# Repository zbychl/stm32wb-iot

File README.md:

# STM32WB based IoT Project
This repisitory keeps components for IoT project based on STM32WB SoC. Project could be used as IoT sensor, effector, bridge, etc. 

# Project Components
Below there is a list of project components along with their description (PCB design for IoT board - HW, firmware - FW, software - SW, and documentation - DOC) . 

## HW - IoT board based on STM32WB SoC
Board designed for IoT sensor or effector. It is based on STM32WB SoC. Board design supports components listed below. Some of them are optional. 

### HW Components:
* STM32WB55CGU6 - dual ARM SoC with radio (BLE and IEEE 802.15.4)
* SHTC3 - digital (I2C) temperature and humidity sensor
* Switch(es)
* PCB antenna
* CR2032/LIR2032 or CR3032/LIR3032 battery socket
* Pins for external power supplier
* Test Points (TPs) for UART for update
* TPs for UART for console
* TPs for JTAG
* TP for HW reset
* LED(s) for health/status monitoring
* GPIO exposed on pins to support common interface (I2C, SPI, UART)
* TPS630xx for supplying from battery, alternatively, components supporting low voltages could be used
* EEPROM

### PCB details
There is a list of requirements put for PCB:
* Size: tbd
* Stackup:
  * https://jlcpcb.com/impedance
  * Layers: 4
  * Width: 1.6mm
  * Prepeg: 7628 (Fr=4.6)
* Standard SMT elements size: 0402 

## FW
TBD

## SW
TBD

## DOC
TBD

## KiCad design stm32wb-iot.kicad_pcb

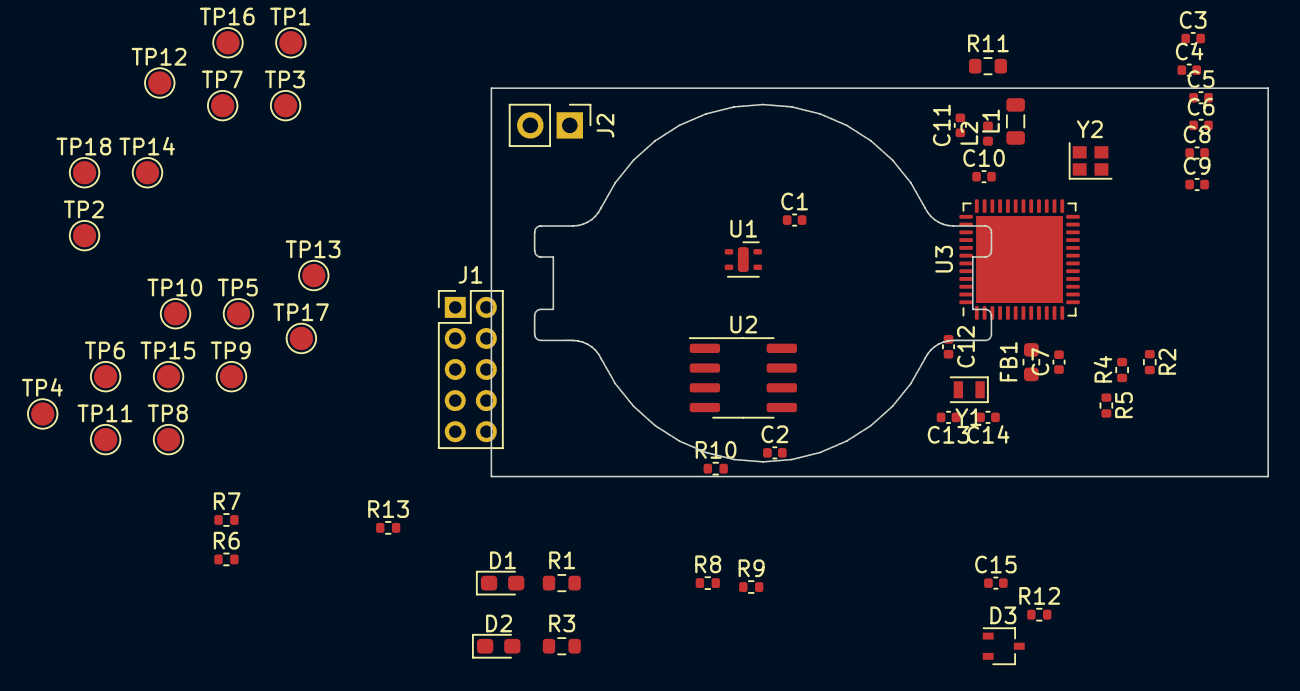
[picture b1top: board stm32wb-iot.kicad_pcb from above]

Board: 4 copper layers, 50.0 x 25.0 mm, 60 parts (1 on the bottom side), 34 nets, no tracks yet.

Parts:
BT1: Battery_Cell; BatteryHolder_Keystone_1057_1x2032
C1, C2, C3, C4, C5, C6, C7, C8, C9, C15: 100n/X5R; C_0402_1005Metric
C10, C11: 4.7uF/X5R; C_0402_1005Metric
C12: 100n\X7R; C_0402_1005Metric
C13, C14: 12pF; C_0402_1005Metric
D1, D2: LED; LED_0603_1608Metric_Pad1.05x0.95mm_HandSolder
D3: BAT54W; SOT-323_SC-70
FB1: 500mA/500mΩ; L_0603_1608Metric
J1: Conn_02x05_Odd_Even; PinHeader_2x05_P2.00mm_Vertical
J2: Conn_01x02_Male; PinHeader_1x02_P2.54mm_Vertical
L1: 10uH/100mA/20%; L_0805_2012Metric
L2: 10uH/500mA/5%; L_0402_1005Metric
R1, R3: 2k; R_0603_1608Metric
R2, R4, R5: 33R; R_0402_1005Metric
R6, R7, R8, R9, R10, R12, R13: 10k; R_0402_1005Metric
R11: 0R/250mW; R_0603_1608Metric
TP1: MISC_RX; TestPoint_Pad_D1.5mm
TP2: MISC_TX; TestPoint_Pad_D1.5mm
TP3, TP6, TP8, TP13, TP18: GND; TestPoint_Pad_D1.5mm
TP4: MISC_SCL; TestPoint_Pad_D1.5mm
TP5: MISC_SDA; TestPoint_Pad_D1.5mm
TP7: MISC_NRST; TestPoint_Pad_D1.5mm
TP9: MISC_BOOT0; TestPoint_Pad_D1.5mm
TP10, TP17: VDD; TestPoint_Pad_D1.5mm
TP11: MISC_IO0; TestPoint_Pad_D1.5mm
TP12: MISC_IO1; TestPoint_Pad_D1.5mm
TP14: SWDIO; TestPoint_Pad_D1.5mm
TP15: SWCLK; TestPoint_Pad_D1.5mm
TP16: NRST; TestPoint_Pad_D1.5mm
U1: SHTC3; Sensirion_DFN-4-1EP_2x2mm_P1mm_EP0.7x1.6mm
U2: M24C02-RMN; SOIC-8_3.9x4.9mm_P1.27mm
U3: STM32WB55Cx; QFN-48-1EP_7x7mm_P0.5mm_EP5.6x5.6mm
Y1: 32.768kHz; Crystal_SMD_2012-2Pin_2.0x1.2mm
Y2: 32MHz; Crystal_SMD_2016-4Pin_2.0x1.6mm

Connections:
/BOOT0: R13.1, TP9.1, U3.4 (PH3-BOOT0)
/IO_IO0: R4.1, U3.10 (PA1)
/IO_IO1: R2.1, U3.15 (PA6)
/IO_LED0: D1.1 (K), U3.17 (PA8)
/IO_LED1: D2.1 (K), U3.37 (PA11)
/IO_PWM: R5.1, U3.9 (PA0)
/MISC_IO0: TP11.1, U3.13 (PA4)
/MISC_IO1: TP12.1, U3.14 (PA5)
/MISC_RX: TP1.1, U3.11 (PA2)
/MISC_SCL: R6.2, TP4.1, U3.16 (PA7)
/MISC_SDA: R7.2, TP5.1, U3.44 (PB4-NJTRST)
/MISC_TX: TP2.1, U3.12 (PA3)
/NRST: D3.3 (K), TP7.1, TP16.1
/SCL_INN: R8.2, U1.2 (SCL), U2.6 (SCL), U3.18 (PA9)
/SDA_INN: R9.2, U1.3 (SDA), U2.5 (SDA), U3.36 (PA10)
/SWCLK: TP15.1, U3.41 (PA14-JTCK_SWCLK)
/SWDIO: TP14.1, U3.39 (PA13-JTMS_SWDIO)
GND: BT1.2 (-), C1.2, C2.2, C3.2, C4.2, C5.2, C6.2, C7.1, C8.2, C9.2, C10.1, C11.2, C12.2, C13.2, C14.2, C15.2, J1.4, J1.6, J1.8, J2.2, R10.2, R13.2, TP3.1, TP6.1, TP8.1, TP13.1, TP18.1, U1.4 (VSS), U2.4 (VSS), U3.22 (VSSRF), U3.32 (VSSSMPS), U3.49 (GNDT), Y2.2, Y2.4
unnamed: C7.2, FB1.2, U3.8 (VDDA)
unnamed: C11.1, L1.1, U3.31 (VFBSMPS)
unnamed: C13.1, U3.2 (PC14-OSC32_IN), Y1.2
unnamed: C14.1, U3.3 (PC15-OSC32_OUT), Y1.1
unnamed: C15.1, D3.1 (A), R12.2, U3.7 (NRST)
unnamed: D1.2 (A), R1.2
unnamed: D2.2 (A), R3.2
unnamed: J1.1, R4.2
unnamed: J1.3, R2.2
unnamed: J1.5, R5.2
unnamed: L1.2, L2.1, R11.2
unnamed: L2.2, U3.33 (VLXSMPS)
unnamed: R10.1, U2.1 (E0), U2.2 (E1), U2.3 (E2)
unnamed: U3.24 (OSC_OUT), Y2.1
unnamed: U3.25 (OSC_IN), Y2.3
VDD: BT1.1 (+), C1.1, C2.1, C3.1, C4.1, C5.1, C6.1, C8.1, C9.1, C10.2, C12.1, FB1.1, J1.2, J1.10, J2.1, R1.1, R3.1, R6.1, R7.1, R8.1, R9.1, R11.1, R12.1, TP10.1, TP17.1, U1.1 (VDD), U2.8 (VCC), U3.1 (VBAT), U3.20 (VDD), U3.23 (VDDRF), U3.34 (VDDSMPS), U3.35 (VDD), U3.48 (VDD)

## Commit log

2022-12-23 Create README.md
    Added README with initial assumptions for Board 1 (IoT based on STM32WB)
2022-12-23 Update README.md
    Temperature sensor changed.
2022-12-24 Update README.md
    Updated battery socket description for board 1
2022-12-26 Update README.md
    Update after repo names change.
    Initial idea was to keep here only HW/PCB designs for different SoCs. Finally decided to keep here all components (hw, fw, sw, doc) for project based on single SoC - STM32WB.
2022-12-26 Update README.md
    Added info about DC/DC converter. If all components support low voltage, it could be dropped to save power and room on PCB.
2022-12-30 Update README.md
    Added EEPROM.
    It shall be one with smallest possible footprint and supportng low power supply voltage (>1.8V), eg. M24C64 or M24C02-R.
2023-01-21 First version for STM32WB project
    v1.00
    TBD.
